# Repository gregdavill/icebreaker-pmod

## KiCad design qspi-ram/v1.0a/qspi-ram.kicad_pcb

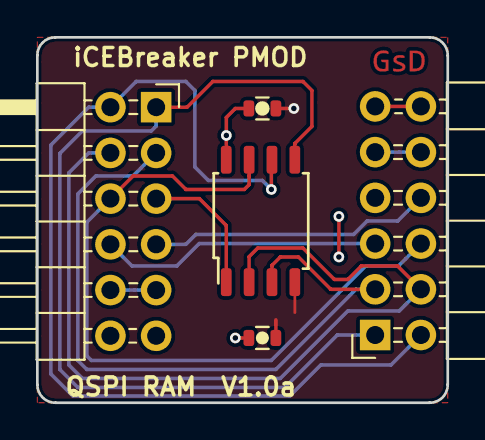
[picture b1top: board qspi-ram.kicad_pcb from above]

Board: 2 copper layers, 22.8 x 20.3 mm, 5 parts (0 on the bottom side), 10 nets.

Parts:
C1: 10u; C_0603
C2: 100n; C_0603
J1, J2: PMOD; PMODHeader_2x06_P2.54mm_Horizontal
U1: W25Q; SOIC-8_5.3x5.3mm_Pitch1.27mm

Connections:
+3V3: C1.1, C2.1, J1.6, J1.12, J2.6, J2.12, U1.8
/CLK: J1.7, J2.7, U1.6
/CS0: J1.3, U1.1
/CS1: J1.10, J2.3
/CS2: J1.4, J2.10
/D0: J1.1, J2.1, U1.5
/D1: J1.8, J2.8, U1.2
/D2: J1.2, J2.2, U1.3
/D3: J1.9, J2.9, U1.7
GND: C1.2, C2.2, J1.5, J1.11, J2.5, J2.11, U1.4

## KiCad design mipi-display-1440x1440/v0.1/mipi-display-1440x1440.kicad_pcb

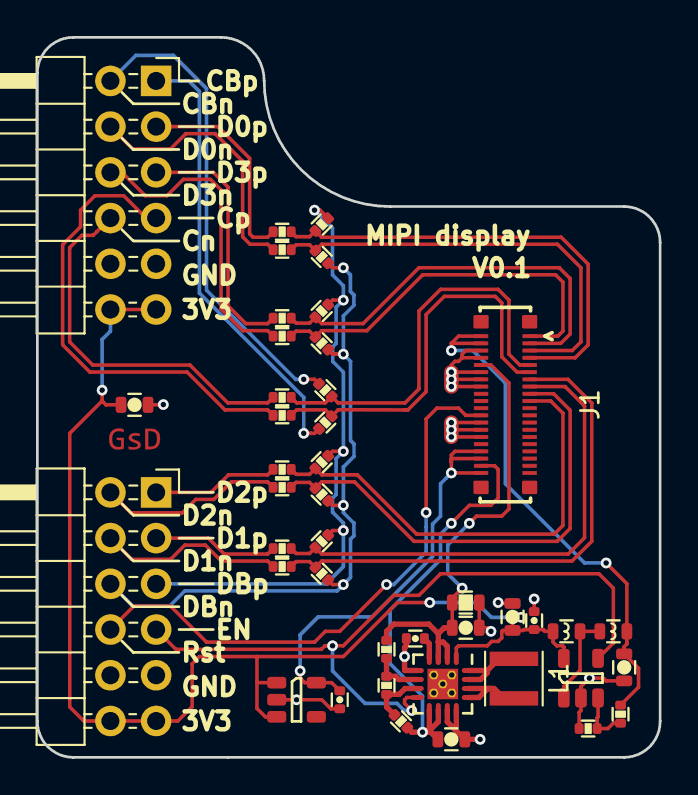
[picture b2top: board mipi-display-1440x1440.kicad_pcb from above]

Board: 2 copper layers, 34.6 x 40.0 mm, 43 parts (0 on the bottom side), 39 nets.

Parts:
C1, C2, C4, C5: 10u; C_0603
C3, C6, C8: 100n; C_0402
C7: 1u; C_0603
D1: SS14; L_0603
J1: JAE-WP7B-P040VA1; WP7B-S040VA1
J2, J4: PMOD; PMODHeader_2x06_P2.54mm_Horizontal
L1: 2.2uH; L_Taiyo-Yuden_MD-3030
L2: 10uH; L_0603
R1, R2, R3, R4, R5, R6, R7, R8, R9, R10: 220R; R_0402
R11, R12, R13, R14, R15, R16, R17, R18, R19, R20: 47R; R_0402
R21, R22, R23, R25, R26: --; R_0402
R24: 550R; R_0603
U1: TPS65135; QFN-16-1EP_3x3mm_Pitch0.5mm
U2: AP3015; SOT-23-5
U3: 1V8; SOT-23-5

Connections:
+1V8: C8.1, J1.21, J1.23, J1.24, U3.5
+3V3: C1.1, C2.1, C6.1, J2.6, J2.12, J4.6, J4.12, L2.2, U1.1, U2.5, U3.1, U3.3
/AVDD: C4.1, J1.22, R21.1, U1.9, U1.10
/AVDD_EN: J2.4, U1.8, U2.4
/AVEE: C5.2, J1.36, R23.2, R24.2, U1.2, U1.3
/CLK_BIAS_N: J4.7, R11.2
/CLK_BIAS_P: J4.1, R12.2
/CLK_N: J4.10, R5.2
/CLK_P: J4.4, R6.2
/D0_N: J4.8, R3.2
/D0_P: J4.2, R4.2
/D1_N: J2.8, R7.2
/D1_P: J2.2, R8.2
/D2_N: J2.7, R9.2
/D2_P: J2.1, R10.2
/D3_N: J4.9, R1.2
/D3_P: J4.3, R2.2
/DAT_BIAS_N: J2.9, R13.2, R15.2, R17.2, R19.2
/DAT_BIAS_P: J2.3, R14.2, R16.2, R18.2, R20.2
/DSIA_CLK_N: J1.5, R5.1, R11.1
/DSIA_CLK_P: J1.6, R6.1, R12.1
/DSIA_D0_N: J1.3, R3.1, R15.1
/DSIA_D0_P: J1.4, R4.1, R16.1
/DSIA_D1_N: J1.7, R7.1, R17.1
/DSIA_D1_P: J1.8, R8.1, R18.1
/DSIA_D2_N: J1.9, R9.1, R19.1
/DSIA_D2_P: J1.10, R10.1, R20.1
/DSIA_D3_N: J1.1, R1.1, R13.1
/DSIA_D3_P: J1.2, R2.1, R14.1
/LED+: C7.1, D1.1, J1.39, J1.40, R25.1
/RESX: J1.29, J2.10
GND: C1.2, C2.2, C3.2, C4.2, C5.1, C6.2, C7.2, C8.2, J1.26, J1.27, J1.28, J1.33, J1.34, J1.35, J1.37, J1.38, J2.5, J2.11, J4.5, J4.11, R24.1, R26.2, U1.5, U1.11, U1.12, U1.17, U2.2, U3.2
unnamed: C3.1, U1.4
unnamed: D1.2, L2.1, U2.1
unnamed: L1.1, U1.15, U1.16
unnamed: L1.2, U1.13, U1.14
unnamed: R21.2, R22.1, U1.7
unnamed: R22.2, R23.1, U1.6
unnamed: R25.2, R26.1, U2.3

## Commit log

2018-11-04 Initial commit of MIPI display board.
2018-11-04 Initial commit of QSPI RAM PMOD.

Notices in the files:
mipi-display-1440x1440/v0.1/mipi-display-1440x1440.kicad_pcb:
License: CC-BY-SA 4.0
qspi-ram/v1.0a/qspi-ram.kicad_pcb:
(C) 2018 Greg Davill
License: CC-BY-SA V4.0
